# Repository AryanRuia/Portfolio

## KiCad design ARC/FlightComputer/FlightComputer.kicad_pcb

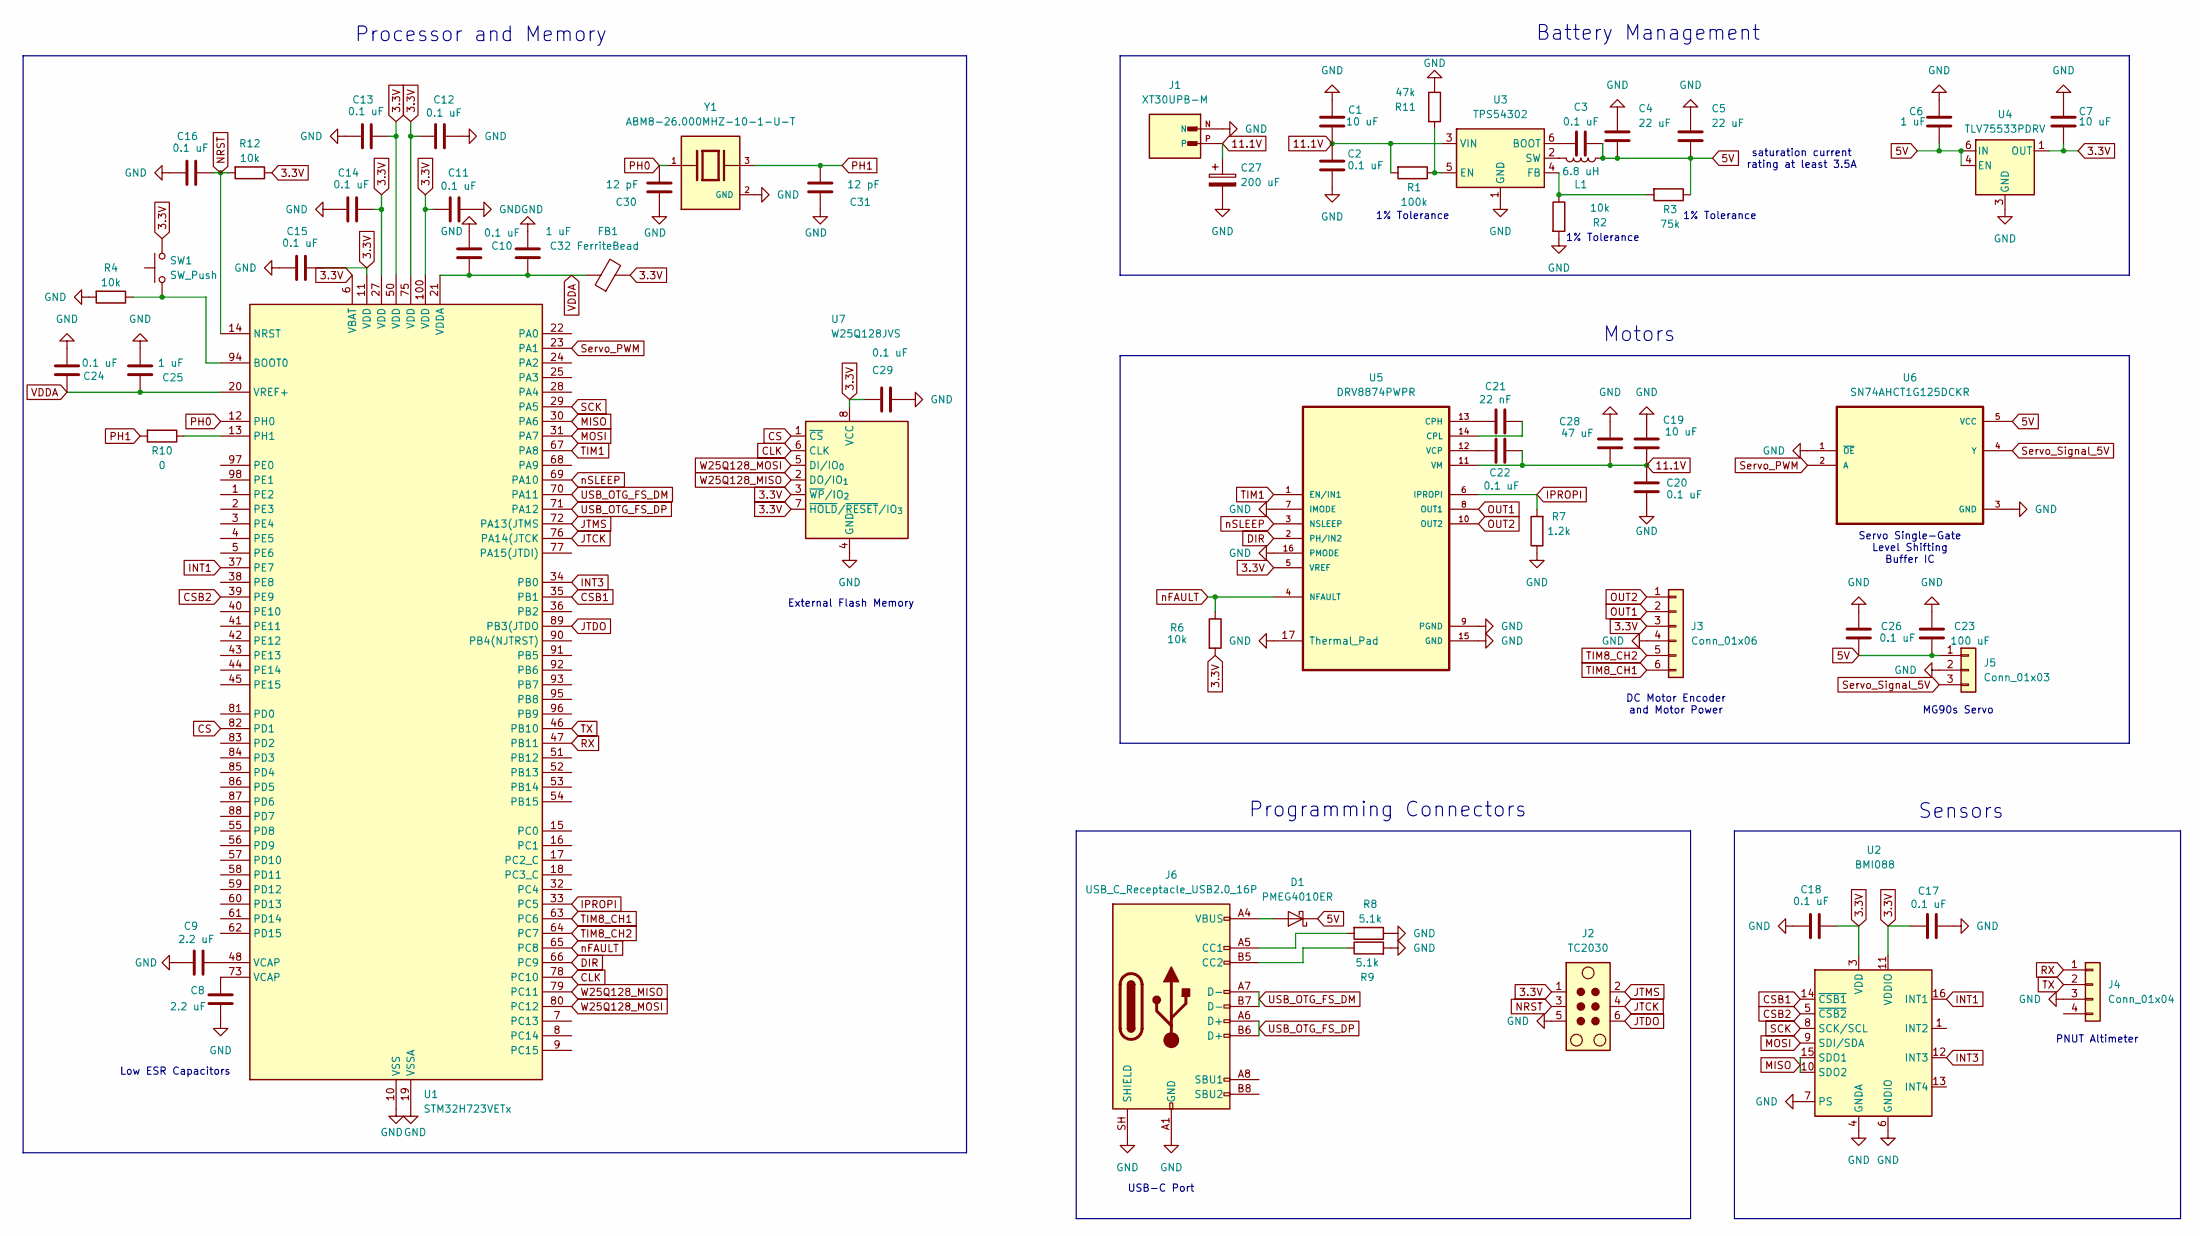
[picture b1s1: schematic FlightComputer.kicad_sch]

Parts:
C1, C7, C19: 10 uF; C_1206_3216Metric
C2, C3, C10, C11, C12, C13, C14, C15, C16, C17, C18, C20, C22, C24, C26, C29: 0.1 uF; C_0603_1608Metric
C4, C5: 22 uF; C_1210_3225Metric
C6, C25: 1 uF; C_0805_2012Metric
C8, C9: 2.2 uF; C_0805_2012Metric
C21: 22 nF; C_0603_1608Metric
C23: 100 uF; C_1812_4532Metric
C27: 200 uF; CP_Elec_8x10
C28: 47 uF; C_1812_4532Metric
C30, C31: 12 pF; C_0603_1608Metric
C32: 1 uF; C_0603_1608Metric
D1: PMEG4010ER; Nexperia_CFP3_SOD-123W
FB1: FerriteBead; L_0603_1608Metric
J1: XT30UPB-M; AMASS_XT30UPB-M
J2: TC2030; Tag-Connect_TC2030-IDC-NL_2x03_P1.27mm_Vertical
J3: Conn_01x06; JST_GH_BM06B-GHS-TBT_1x06-1MP_P1.25mm_Vertical
J4: Conn_01x04; JST_GH_BM04B-GHS-TBT_1x04-1MP_P1.25mm_Vertical
J5: Conn_01x03; JST_GH_BM03B-GHS-TBT_1x03-1MP_P1.25mm_Vertical
J6: USB_C_Receptacle_USB2.0_16P; USB_C_Receptacle_HRO_TYPE-C-31-M-12
L1: 6.8 uH; L_Bourns_SRP5030T
R1: 100k; R_0603_1608Metric
R2, R4, R6, R12: 10k; R_0603_1608Metric
R3: 75k; R_0603_1608Metric
R7: 1.2k; R_0805_2012Metric
R8, R9: 5.1k; R_0603_1608Metric
R10: 0; R_0603_1608Metric
R11: 47k; R_0603_1608Metric
SW1: SW_Push; SW_SPST_B3U-1000P
U1: STM32H723VETx; LQFP-100_14x14mm_P0.5mm
U2: BMI088; Bosch_LGA-16_4.5x3mm_P0.5mm_LayoutBorder7x1y_ClockwisePinNu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
U3: TPS54302; SOT-23-6
U4: TLV75533PDRV; WSON-6-1EP_2x2mm_P0.65mm_EP1x1.6mm
U5: DRV8874PWPR; SOP65P640X120-17N
U6: SN74AHCT1G125DCKR; SOT65P210X110-5N
U7: W25Q128JVS; SOIC-8_5.3x5.3mm_P1.27mm
Y1: ABM8-26.000MHZ-10-1-U-T; XTAL_ABM8-26.000MHZ-10-1-U-T; PARTREV 44041

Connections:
3.3V: C7.2, C11.2, C12.2, C13.2, C14.2, C15.2, C17.2, C18.2, C29.2, FB1.2, J2.1, J3.3, R6.2, R12.1, SW1.2, U1.6 (VBAT), U1.11 (VDD), U1.27 (VDD), U1.50 (VDD), U1.75 (VDD), U1.100 (VDD), U2.3 (VDD), U2.11 (VDDIO), U4.1 (OUT), U5.5 (VREF), U7.3 (~WP/IO_{2}), U7.7 (~HOLD/~RESET/IO_{3}), U7.8 (VCC)
5V: C3.2, C4.2, C5.2, C6.2, C23.1, C26.1, D1.1 (K), J5.1, L1.1, R3.1, U4.4 (EN), U4.6 (IN), U6.5 (VCC)
11.1V: C1.1, C2.1, C19.1, C20.1, C22.1, C27.1, C28.1, J1.P, R1.2, U3.3 (VIN), U5.11 (VM)
CLK: U1.78 (PC10), U7.6 (CLK)
CS: U1.82 (PD1), U7.1 (~CS)
CSB1: U1.35 (PB1), U2.14 (~CSB1)
CSB2: U1.39 (PE9), U2.5 (~CSB2)
DIR: U1.66 (PC9), U5.2 (PH/IN2)
GND: C1.2, C2.2, C4.1, C5.1, C6.1, C7.1, C8.1, C9.2, C10.1, C11.1, C12.1, C13.1, C14.1, C15.1, C16.1, C17.1, C18.1, C19.2, C20.2, C23.2, C24.1, C25.1, C26.2, C27.2, C28.2, C29.1, C30.2, C31.2, C32.1, J1.N, J2.5, J3.4, J4.3, J5.2, J6.A1 (GND), J6.A12 (GND), J6.B1 (GND), J6.B12 (GND), J6.SH (SHIELD), R2.2, R4.2, R7.1, R8.1, R9.2, R11.1, U1.10 (VSS), U1.19 (VSSA), U1.26 (VSS), U1.49 (VSS), U1.74 (VSS), U1.99 (VSS), U2.2 (GNDA), U2.4 (GNDA), U2.6 (GNDIO), U2.7 (PS), U3.1 (GND), U4.3 (GND), U4.7 (GND), U5.7 (IMODE), U5.9 (PGND), U5.15 (GND), U5.16 (PMODE), U5.17 (Thermal_Pad), U6.1 (~OE), U6.3 (GND), U7.4 (GND), Y1.2 (GND), Y1.4 (GND)
INT1: U1.37 (PE7), U2.16 (INT1)
INT3: U1.34 (PB0), U2.12 (INT3)
IPROPI: R7.2, U1.33 (PC5), U5.6 (IPROPI)
JTCK: J2.4, U1.76 (PA14(JTCK)
JTDO: J2.6, U1.89 (PB3(JTDO)
JTMS: J2.2, U1.72 (PA13(JTMS)
MISO: U1.30 (PA6), U2.10 (SDO2), U2.15 (SDO1)
MOSI: U1.31 (PA7), U2.9 (SDI/SDA)
NRST: C16.2, J2.3, R12.2, U1.14 (NRST)
unnamed: C8.2, U1.73 (VCAP)
unnamed: C9.1, U1.48 (VCAP)
unnamed: D1.2 (A), J6.A4 (VBUS), J6.A9 (VBUS), J6.B4 (VBUS), J6.B9 (VBUS)
unnamed: J6.A5 (CC1), R8.2
unnamed: J6.B5 (CC2), R9.1
unnamed: R4.1, SW1.1, U1.94 (BOOT0)
unnamed: R10.1, U1.13 (PH1)
unnamed: C3.1, U3.6 (BOOT)
unnamed: R1.1, R11.2, U3.5 (EN)
unnamed: R2.1, R3.2, U3.4 (FB)
unnamed: L1.2, U3.2 (SW)
unnamed: C21.2, U5.13 (CPH)
unnamed: C21.1, U5.14 (CPL)
unnamed: C22.2, U5.12 (VCP)
OUT1: J3.2, U5.8 (OUT1)
OUT2: J3.1, U5.10 (OUT2)
PH0: C30.1, U1.12 (PH0), Y1.1
PH1: C31.1, R10.2, Y1.3
RX: J4.1, U1.47 (PB11)
SCK: U1.29 (PA5), U2.8 (SCK/SCL)
Servo_PWM: U1.23 (PA1), U6.2 (A)
Servo_Signal_5V: J5.3, U6.4 (Y)
TIM1: U1.67 (PA8), U5.1 (EN/IN1)
TIM8_CH1: J3.6, U1.63 (PC6)
TIM8_CH2: J3.5, U1.64 (PC7)
TX: J4.2, U1.46 (PB10)
USB_OTG_FS_DM: J6.A7 (D-), J6.B7 (D-), U1.70 (PA11)
USB_OTG_FS_DP: J6.A6 (D+), J6.B6 (D+), U1.71 (PA12)
VDDA: C10.2, C24.2, C25.2, C32.2, FB1.1, U1.20 (VREF+), U1.21 (VDDA)
W25Q128_MISO: U1.79 (PC11), U7.2 (DO/IO_{1})
W25Q128_MOSI: U1.80 (PC12), U7.5 (DI/IO_{0})
nFAULT: R6.1, U1.65 (PC8), U5.4 (NFAULT)
nSLEEP: U1.69 (PA10), U5.3 (NSLEEP)

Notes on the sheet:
PNUT Altimeter
1% Tolerance
Motors
Servo Single-Gate Level Shifting Buffer IC
Battery Management
Processor and Memory
saturation current rating at least 3.5A
External Flash Memory
USB-C Port
MG90s Servo
Sensors
DC Motor Encoder and Motor Power
Low ESR Capacitors
Programming Connectors

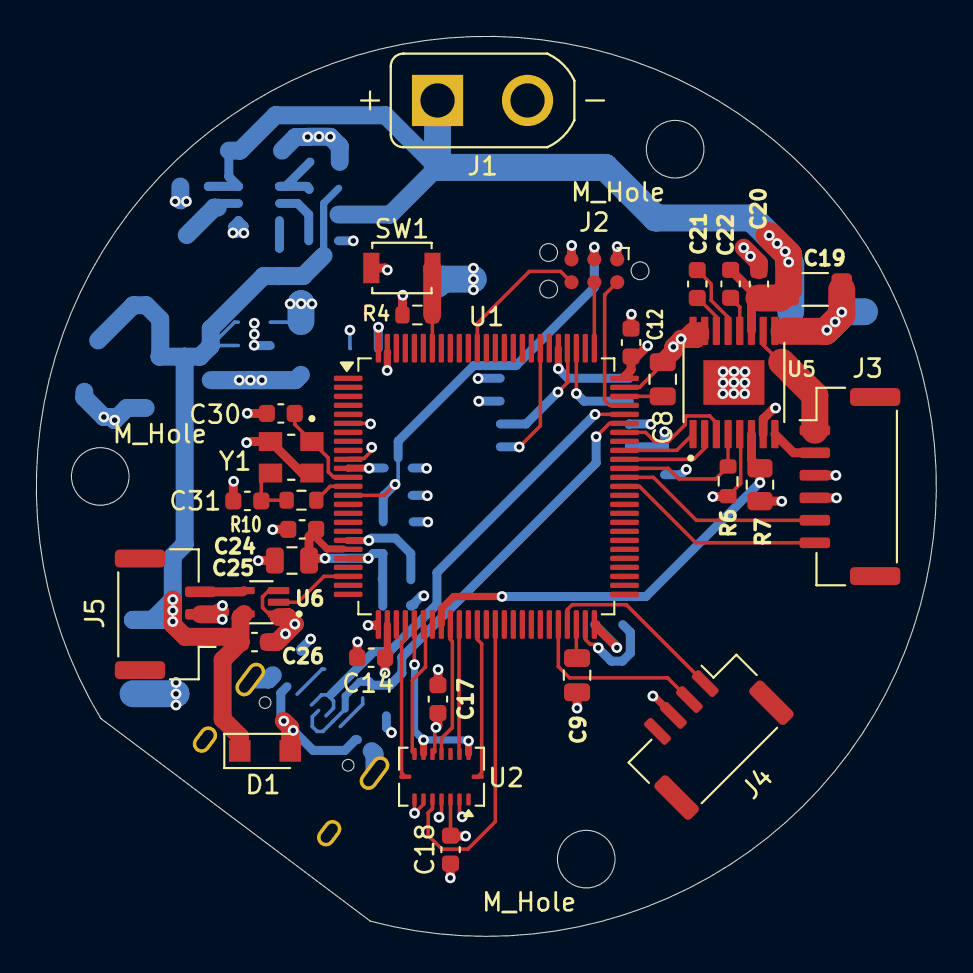
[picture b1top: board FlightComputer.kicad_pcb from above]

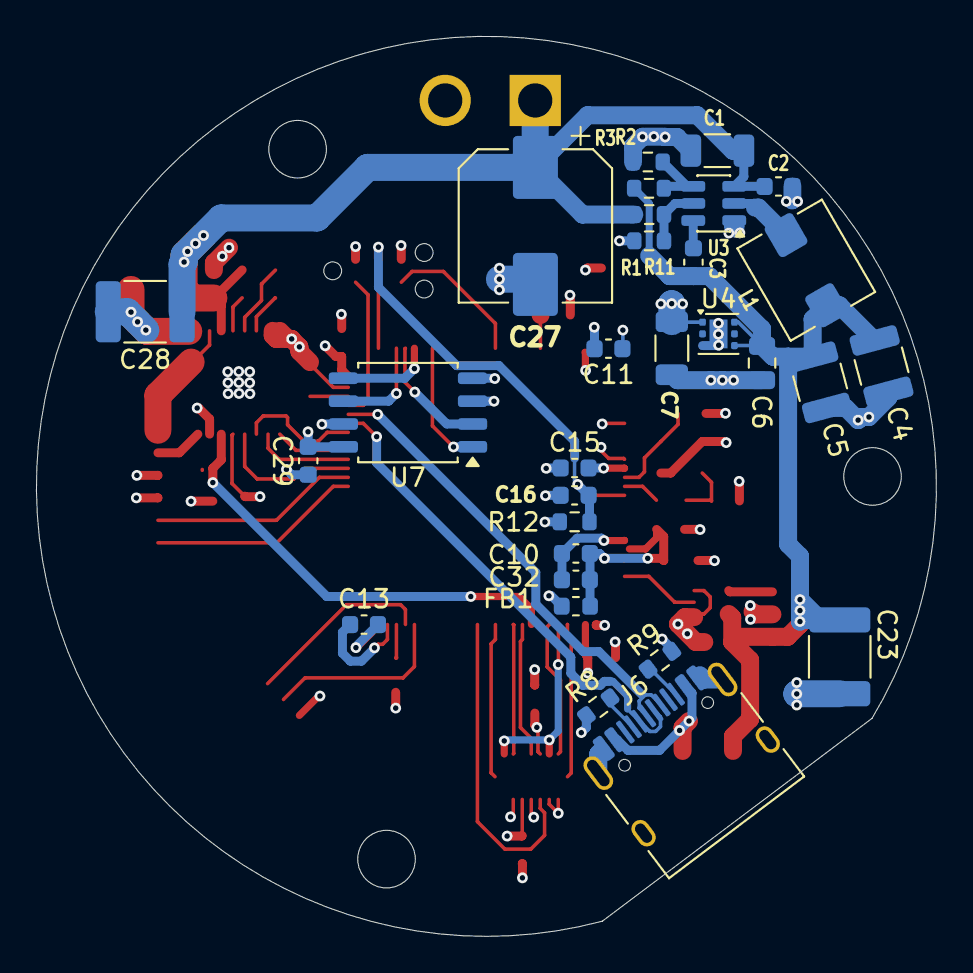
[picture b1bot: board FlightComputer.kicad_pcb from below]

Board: 4 copper layers, 50.0 x 50.0 mm, 64 parts (30 on the bottom side), 51 nets.

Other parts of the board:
M_Hole: MountingHole_3.2mm_M3
M_Hole#2, M_Hole#3: MountingHole_3.2mm_M3

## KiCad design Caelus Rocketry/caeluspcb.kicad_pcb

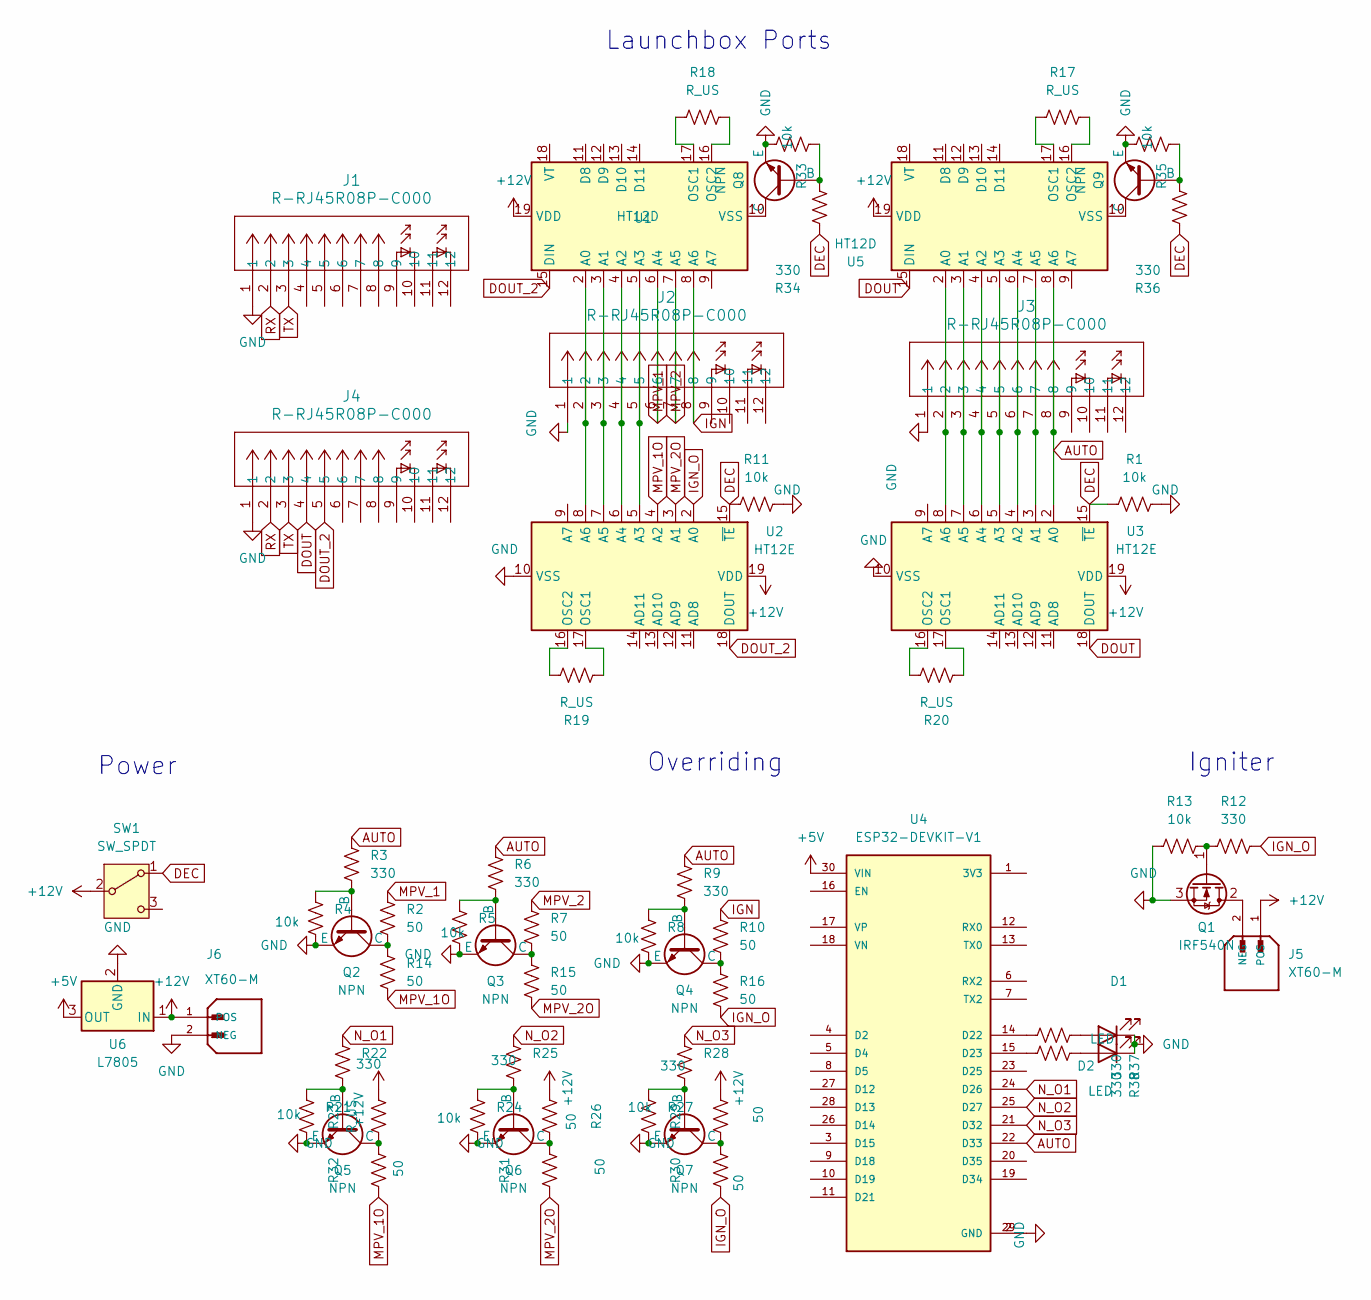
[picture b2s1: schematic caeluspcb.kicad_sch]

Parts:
D1, D2: LED; LED_D3.0mm
J1, J2, J3, J4: R-RJ45R08P-C000; CONN12_R-RJ45_CKM
J5: XT60-M; JST_EH_B2B-EH-A_1x02_P2.50mm_Vertical
J6: XT60-M; AMASS_XT60-M_1x02_P7.20mm_Vertical
Q1: IRF540N; TO-220-3_Vertical
Q2, Q3, Q4, Q5, Q6, Q7, Q8, Q9: NPN; TO-92
R1, R4, R5, R8, R11, R13, R21, R24, R27, R33, R35: 10k; R_Axial_DIN0207_L6.3mm_D2.5mm_P10.16mm_Horizontal
R2, R7, R10, R14, R15, R16, R26, R29, R30, R31, R32: 50; R_Axial_DIN0207_L6.3mm_D2.5mm_P10.16mm_Horizontal
R3, R6, R9, R12, R22, R25, R28, R34, R36, R37, R38: 330; R_Axial_DIN0207_L6.3mm_D2.5mm_P10.16mm_Horizontal
R17, R18, R19, R20, R23: R_US; R_Axial_DIN0207_L6.3mm_D2.5mm_P10.16mm_Horizontal
SW1: SW_SPDT; SPDT_Slide_Switch
U1, U5: HT12D; CERDIP-18_W7.62mm_SideBrazed
U2, U3: HT12E; CERDIP-18_W7.62mm_SideBrazed
U4: ESP32-DEVKIT-V1; MODULE_ESP32_DEVKIT_V1; PARTREV N/A
U6: L7805; TO-220-3_Vertical

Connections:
+5V: U4.30 (VIN), U6.3 (OUT)
+12V: J5.1 (POS), J6.1 (POS), R23.2, R26.2, R29.2, SW1.2 (B), U1.19 (VDD), U2.19 (VDD), U3.19 (VDD), U5.19 (VDD), U6.1 (IN)
AUTO: J3.8, R3.1, R6.1, R9.1, U3.2 (A0), U4.22 (D33), U5.8 (A6)
DEC: R1.1, R11.1, R34.1, R36.1, SW1.1 (A), U2.15 (~TE), U3.15 (~TE)
DOUT: J4.4, U3.18 (DOUT), U5.15 (DIN)
DOUT_2: J4.5, U1.15 (DIN), U2.18 (DOUT)
GND: D1.1 (K), D2.1 (K), J1.1, J2.1, J3.1, J4.1, J6.2 (NEG), Q1.3 (S), Q2.3 (E), Q3.3 (E), Q4.3 (E), Q5.3 (E), Q6.3 (E), Q7.3 (E), Q8.3 (E), Q9.3 (E), R1.2, R4.2, R5.2, R8.2, R11.2, R13.1, R21.2, R24.2, R27.2, R33.2, R35.2, U2.10 (VSS), U3.10 (VSS), U4.2 (GND), U4.29 (GND), U6.2 (GND)
IGN: J2.8, R10.1, U1.8 (A6)
IGN_O: R12.2, R16.2, R30.1, U2.2 (A0)
MPV_1: J2.6, R2.1, U1.6 (A4)
MPV_1O: R14.2, R32.1, U2.4 (A2)
MPV_2: J2.7, R7.1, U1.7 (A5)
MPV_2O: R15.2, R31.1, U2.3 (A1)
N_O1: R22.1, U4.24 (D26)
N_O2: R25.1, U4.25 (D27)
N_O3: R28.1, U4.21 (D32)
unnamed: D1.2 (A), R37.1
unnamed: D2.2 (A), R38.1
unnamed: J5.2 (NEG), Q1.2 (D)
unnamed: Q1.1 (G), R12.1, R13.2
unnamed: Q2.2 (B), R3.2, R4.1
unnamed: Q2.1 (C), R2.2, R14.1
unnamed: Q3.2 (B), R5.1, R6.2
unnamed: Q3.1 (C), R7.2, R15.1
unnamed: Q4.2 (B), R8.1, R9.2
unnamed: Q4.1 (C), R10.2, R16.1
unnamed: Q5.2 (B), R21.1, R22.2
unnamed: Q5.1 (C), R23.1, R32.2
unnamed: Q6.2 (B), R24.1, R25.2
unnamed: Q6.1 (C), R26.1, R31.2
unnamed: Q7.2 (B), R27.1, R28.2
unnamed: Q7.1 (C), R29.1, R30.2
unnamed: Q8.2 (B), R33.1, R34.2
unnamed: Q8.1 (C), U1.10 (VSS)
unnamed: Q9.2 (B), R35.1, R36.2
unnamed: Q9.1 (C), U5.10 (VSS)
unnamed: J2.2, U1.2 (A0), U2.8 (A6)
unnamed: J2.3, U1.3 (A1), U2.7 (A5)
unnamed: J2.4, U1.4 (A2), U2.6 (A4)
unnamed: J2.5, U1.5 (A3), U2.5 (A3)
unnamed: R18.2, U1.17 (OSC1)
unnamed: R18.1, U1.16 (OSC2)
unnamed: R19.2, U2.17 (OSC1)
unnamed: R19.1, U2.16 (OSC2)
unnamed: J3.7, U3.3 (A1), U5.7 (A5)
unnamed: J3.6, U3.4 (A2), U5.6 (A4)
unnamed: J3.5, U3.5 (A3), U5.5 (A3)
unnamed: J3.4, U3.6 (A4), U5.4 (A2)
unnamed: J3.3, U3.7 (A5), U5.3 (A1)
unnamed: J3.2, U3.8 (A6), U5.2 (A0)
unnamed: R20.2, U3.17 (OSC1)
unnamed: R20.1, U3.16 (OSC2)
unnamed: R37.2, U4.14 (D22)
unnamed: R38.2, U4.15 (D23)
unnamed: R17.2, U5.17 (OSC1)
unnamed: R17.1, U5.16 (OSC2)
RX: J1.2, J4.2
TX: J1.3, J4.3

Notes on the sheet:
Power
Igniter
Overriding
Launchbox Ports

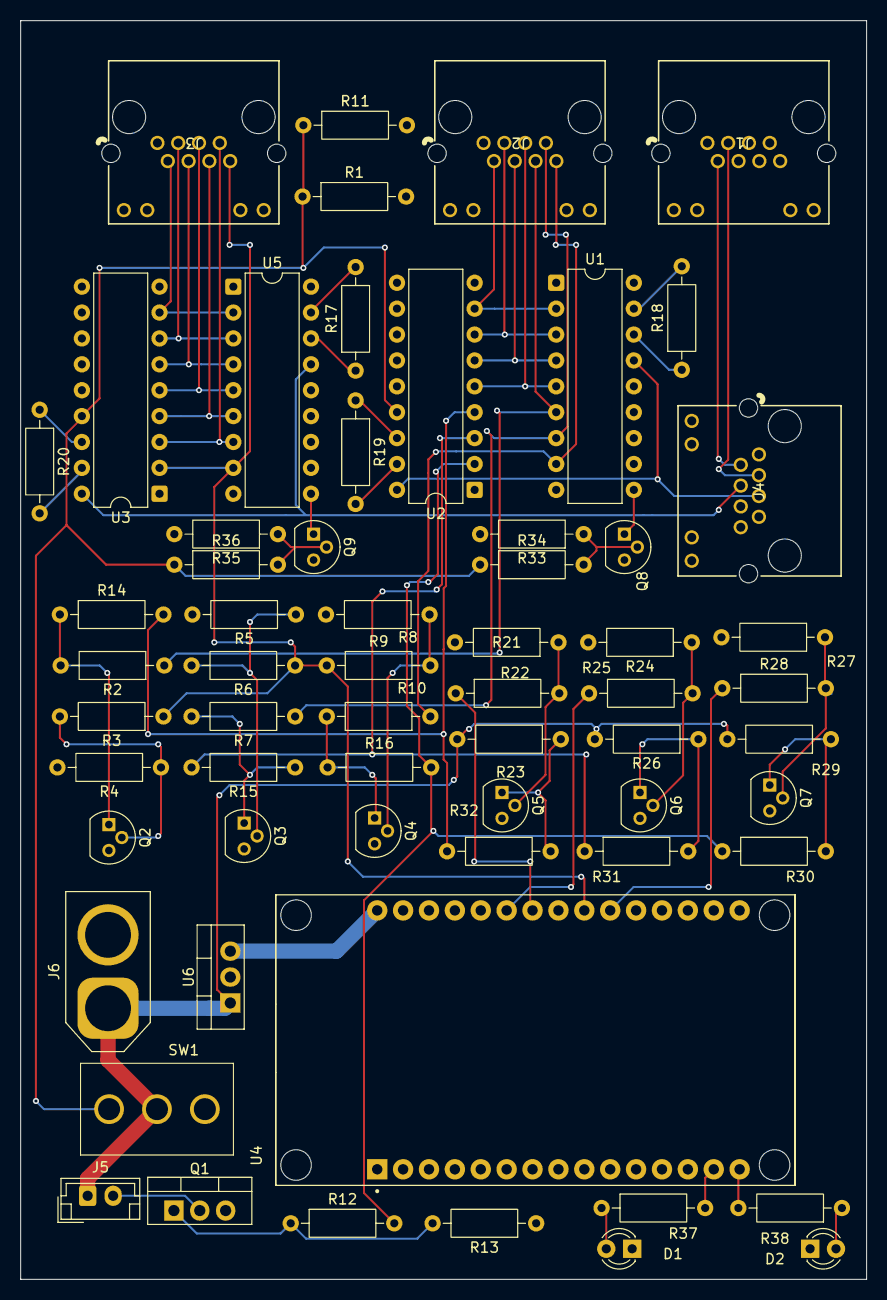
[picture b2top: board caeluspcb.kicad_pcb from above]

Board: 2 copper layers, 83.0 x 123.5 mm, 62 parts (0 on the bottom side), 58 nets.

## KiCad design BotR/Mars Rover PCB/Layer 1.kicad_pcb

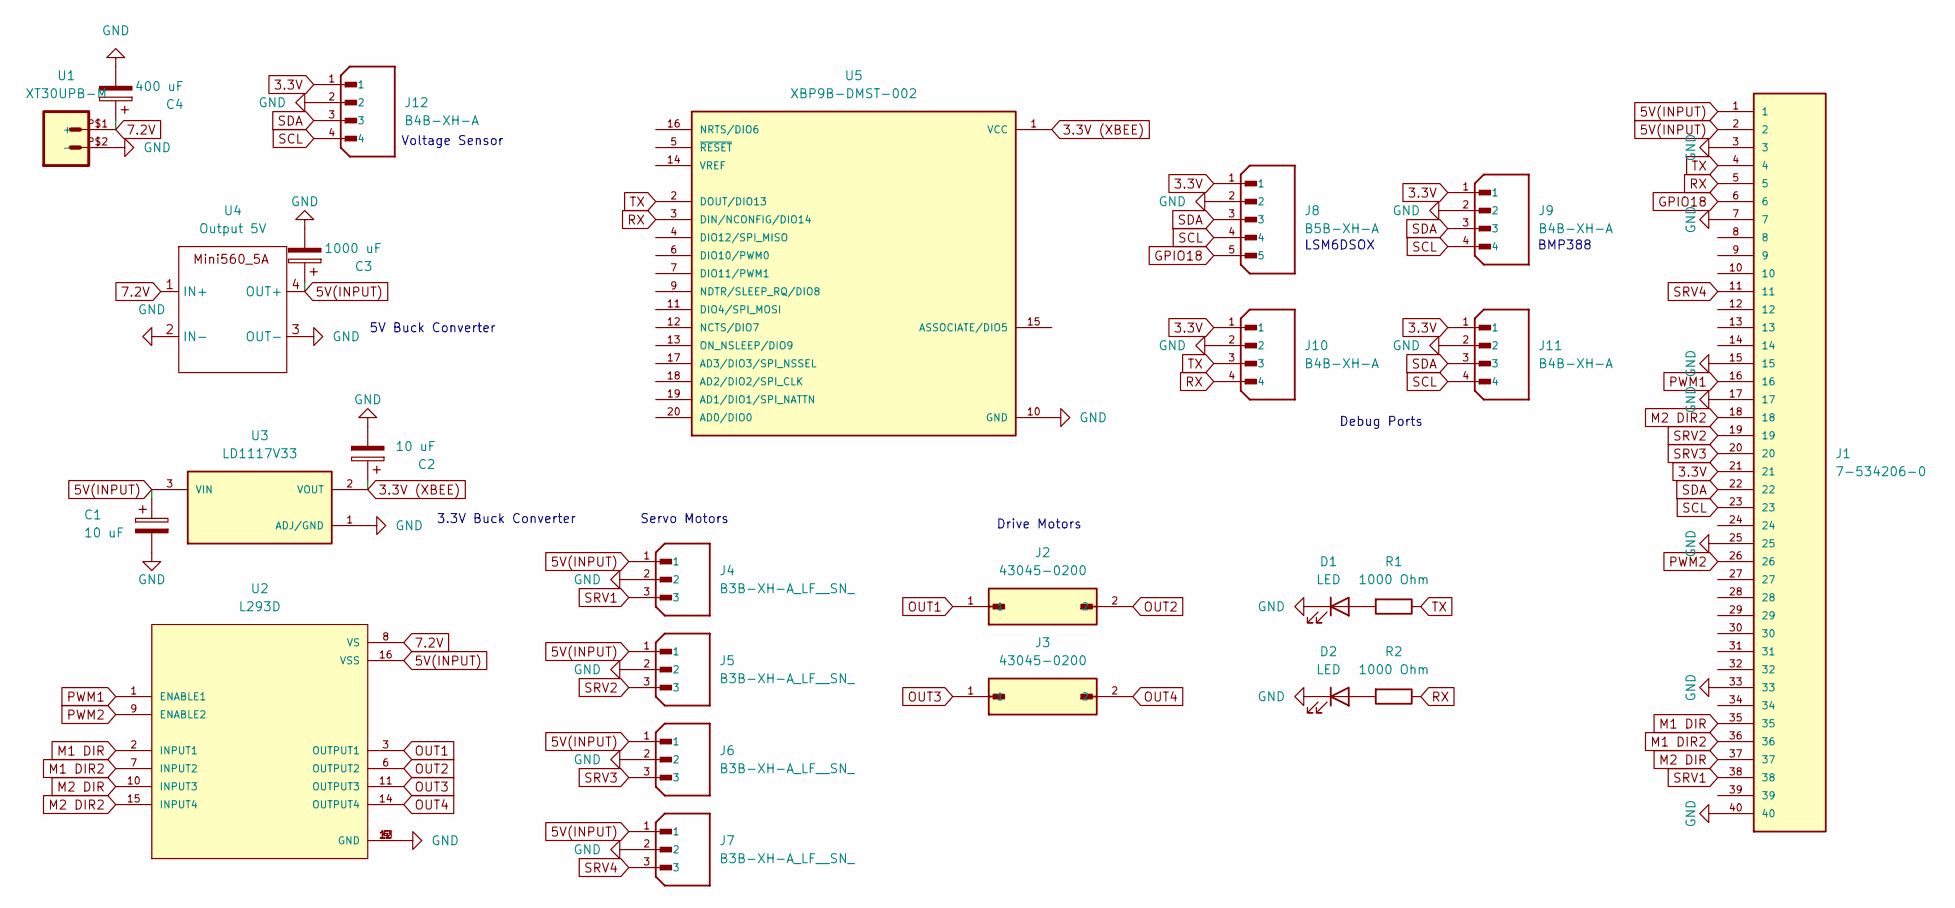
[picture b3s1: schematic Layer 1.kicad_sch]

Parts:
C1, C2: 10 uF; CP_Radial_Tantal_D4.5mm_P2.50mm
C3: 1000 uF; CP_Radial_D10.0mm_P5.00mm
C4: 400 uF; CP_Radial_D8.0mm_P3.50mm
D1, D2: LED; LED_D3.0mm
J1: 7-534206-0; TE_7-534206-0; PARTREV R
J2, J3: 43045-0200; MOLEX_43045-0200; PARTREV G
J4, J5, J6, J7: B3B-XH-A_LF__SN_; JST_B3B-XH-A_LF__SN_; PARTREV 7/4/21
J8: B5B-XH-A; JST_XH_B5B-XH-A_1x05_P2.50mm_Vertical; PARTREV 7/4/21
J9, J10, J11, J12: B4B-XH-A; JST_XH_B4B-XH-A_1x04_P2.50mm_Vertical; PARTREV 7/4/21
R1, R2: 1000 Ohm; R_Axial_DIN0207_L6.3mm_D2.5mm_P7.62mm_Horizontal
U1: XT30UPB-M
U2: L293D; DIP880W50P254L2000H510Q16
U3: LD1117V33; TO-220-3_Vertical; PARTREV 37
U4: Output 5V; Mini560
U5: XBP9B-DMST-002; DIP2200W51P200L3294H279Q20P

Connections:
3.3V: J1.21, J8.1, J9.1, J10.1, J11.1, J12.1
3.3V (XBEE): C2.1, U3.2 (VOUT), U5.1 (VCC)
5V(INPUT): C1.1, C3.1, J1.1, J1.2, J4.1, J5.1, J6.1, J7.1, U2.16 (VSS), U3.3 (VIN), U4.4 (OUT+)
7.2V: C4.1, U1.P$1 (+), U2.8 (VS), U4.1 (IN+)
GND: C1.2, C2.2, C3.2, C4.2, D1.1 (K), D2.1 (K), J1.3, J1.7, J1.15, J1.17, J1.25, J1.33, J1.40, J4.2, J5.2, J6.2, J7.2, J8.2, J9.2, J10.2, J11.2, J12.2, U1.P$2 (-), U2.4 (GND), U2.5 (GND), U2.12 (GND), U2.13 (GND), U3.1 (ADJ/GND), U4.2 (IN-), U4.3 (OUT-), U5.10 (GND)
GPIO18: J1.6, J8.5
M1 DIR: J1.35, U2.2 (INPUT1)
M1 DIR2: J1.36, U2.7 (INPUT2)
M2 DIR: J1.37, U2.10 (INPUT3)
M2 DIR2: J1.18, U2.15 (INPUT4)
unnamed: D1.2 (A), R1.2
unnamed: D2.2 (A), R2.2
OUT1: J2.1, U2.3 (OUTPUT1)
OUT2: J2.2, U2.6 (OUTPUT2)
OUT3: J3.1, U2.11 (OUTPUT3)
OUT4: J3.2, U2.14 (OUTPUT4)
PWM1: J1.16, U2.1 (ENABLE1)
PWM2: J1.26, U2.9 (ENABLE2)
RX: J1.5, J10.4, R2.1, U5.3 (DIN/NCONFIG/DIO14)
SCL: J1.23, J8.4, J9.4, J11.4, J12.4
SDA: J1.22, J8.3, J9.3, J11.3, J12.3
SRV1: J1.38, J4.3
SRV2: J1.19, J5.3
SRV3: J1.20, J6.3
SRV4: J1.11, J7.3
TX: J1.4, J10.3, R1.1, U5.2 (DOUT/DIO13)

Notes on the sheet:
Voltage Sensor
Servo Motors
3.3V Buck Converter
LSM6DSOX
5V Buck Converter
BMP388
Debug Ports
Drive Motors

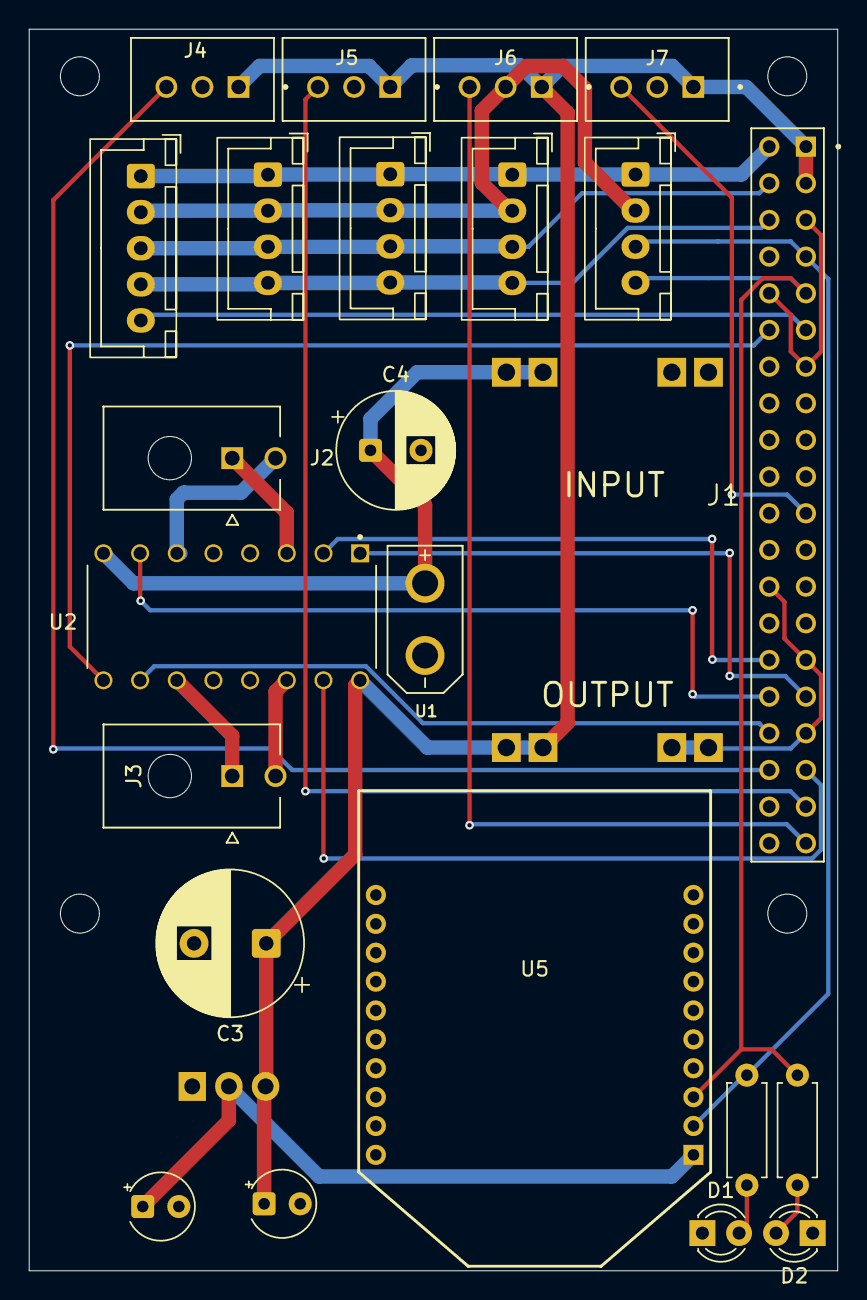
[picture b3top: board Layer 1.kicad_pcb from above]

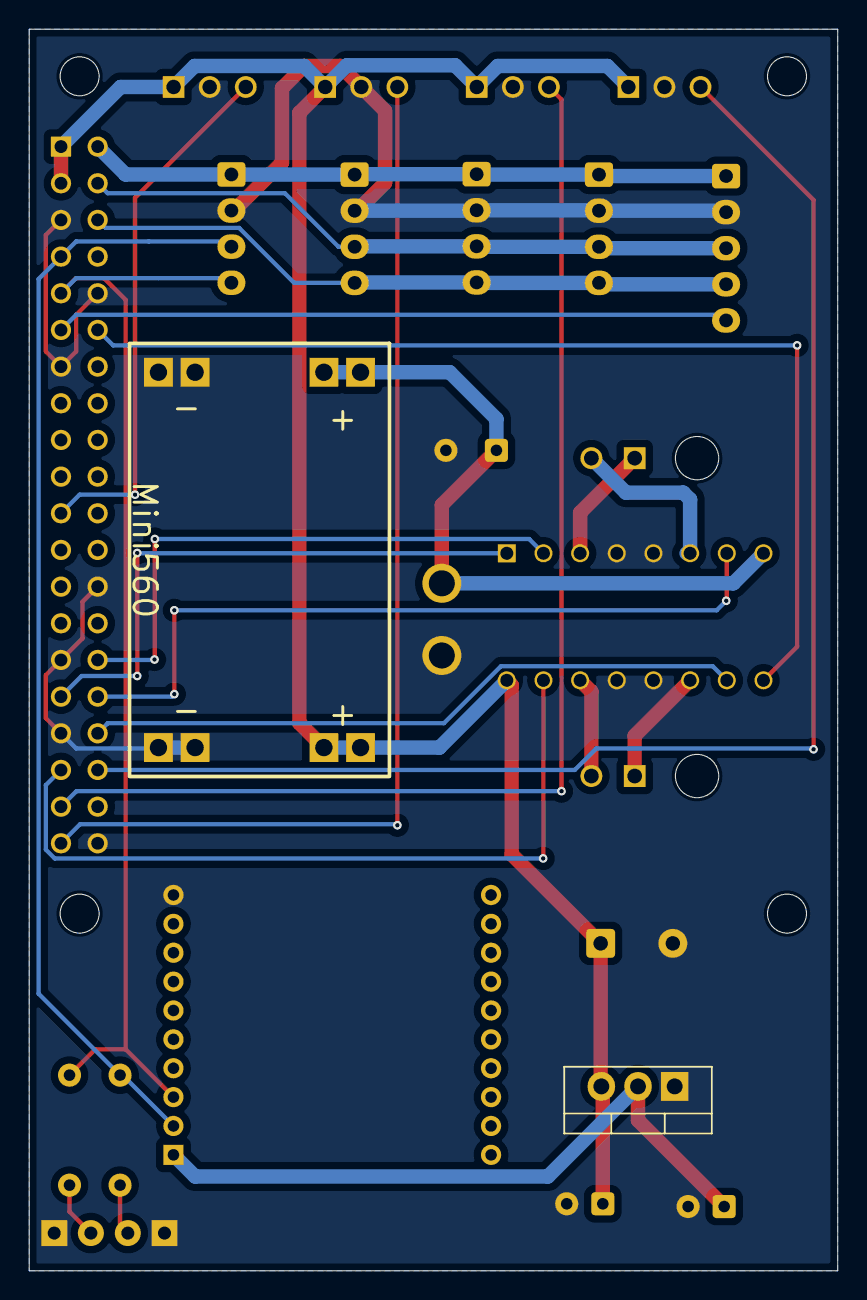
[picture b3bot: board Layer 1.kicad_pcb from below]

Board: 2 copper layers, 56.0 x 86.0 mm, 25 parts (2 on the bottom side), 26 nets.

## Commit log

2026-06-27 organized portfolio files
2026-06-27 Add Zephyr.ork project file
    Adds the new `Junior L1/Zephyr.ork` binary asset to the repository.
2026-06-27 Rename Mars Rover project folders
    Move the Mars Rover code and PCB files into the new `BotR/Mars Rover Code` and `BotR/Mars Rover PCB` directories, preserving existing contents and paths while standardizing the project layout.
2026-06-29 Icarus
2026-06-30 Removed Duplicate
